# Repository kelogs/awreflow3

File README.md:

# AW reflow 3

awreflow3 is a reflow oven for soldering PCBs based on [Andy's Workshop awreflow2](http://andybrown.me.uk/2015/07/12/awreflow2/). Technically, this repository contains the missing electric diagram and a layout for the oven, with some modifications in order to suit the parts I had lying around. The purpose of this repository is that you can also pull the files and modify them according to your needs.

## Prerequisites

This project has been developed with [KiCad](http://www.kicad-pcb.org/download/)

## Notes

If you have to order the MOC3020 from the schematic you could get a [MOC3023](https://www.arrow.com/en/products/moc3023/isocom) instead and do away with the Q2 transistor and adjoining resistors.

Other things worth mentioning on the actual oven. Get one based on halogen heating elements just like Andy has done. Mine is a quartz elements oven and the PID is totally useless due to its very high inertia. I had to bypass the PID and hardcode some time intervals where power level is 0% and others where power is driven at 100%. 
At 1000W power and and 9L volume my oven can still bake a full tray of leaded solder PCBs, only a bit slower than others. Here is how it looks:

**NOTE** I currently have 9 extra PCBs already made. If you would like one drop me a message here and I'll deliver it for $3.44 + shipping + Paypal taxes

## License
[MIT](https://choosealicense.com/licenses/mit/)

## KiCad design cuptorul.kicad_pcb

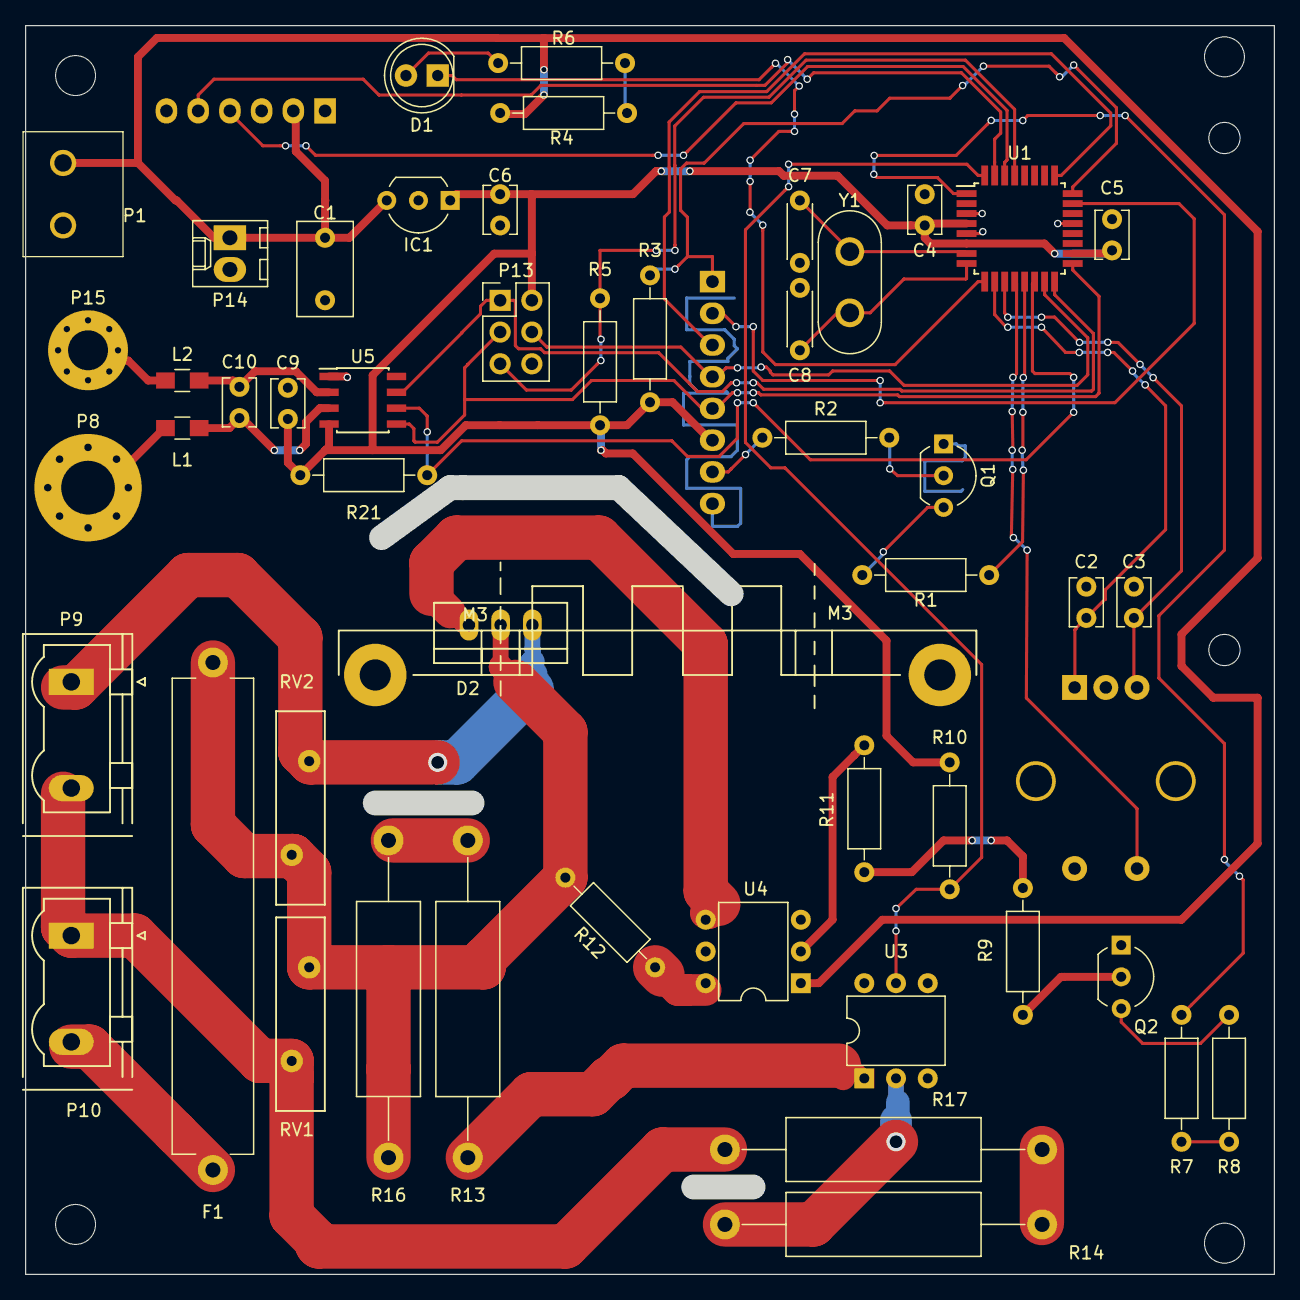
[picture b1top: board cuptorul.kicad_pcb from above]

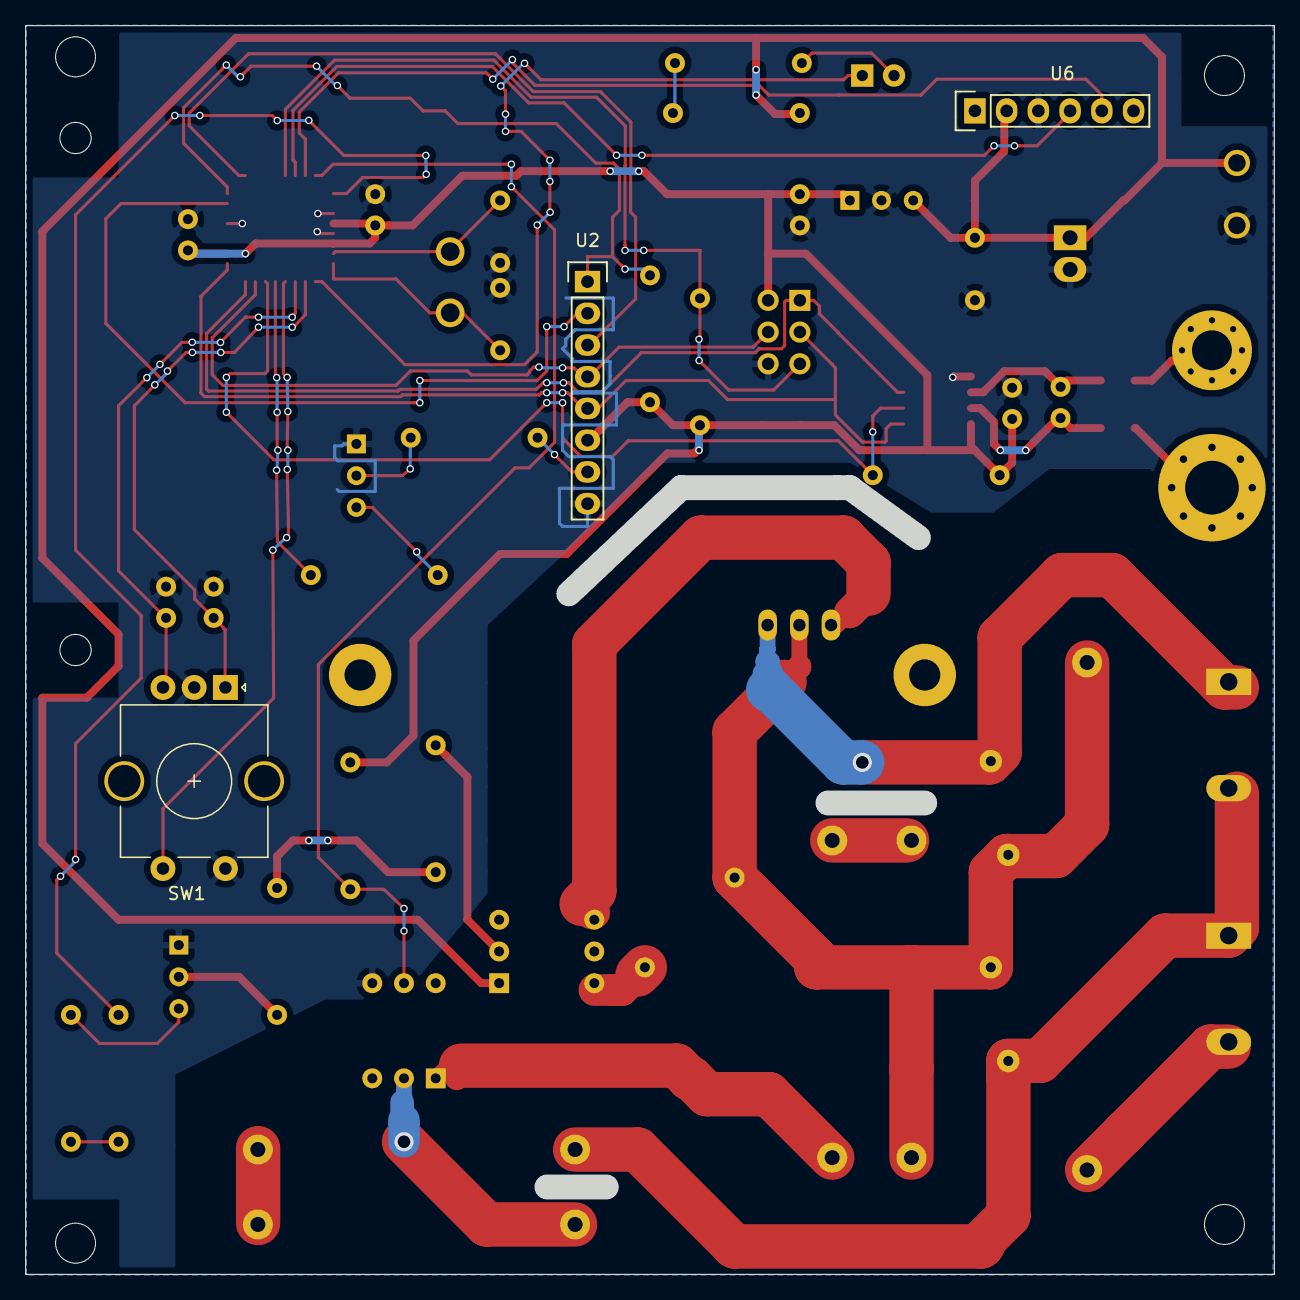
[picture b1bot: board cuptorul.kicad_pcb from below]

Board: 2 copper layers, 98.1 x 98.1 mm, 52 parts (3 on the bottom side), 46 nets.

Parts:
C1: 330nF; C_Disc_D7.5mm_W4.4mm_P5.00mm
C2, C3, C4, C5, C6, C9: 100nF; C_Disc_D3.8mm_W2.6mm_P2.50mm
C7, C8: 24pF; C_Disc_D4.3mm_W1.9mm_P5.00mm
C10: 10nF; C_Disc_D3.8mm_W2.6mm_P2.50mm
D1: LINK; LED_D5.0mm
D2: TRIAC; TO-220_Neutral123_Vertical
F1: Fuse; R_Axial_Power_L38.0mm_W6.4mm_P40.64mm
IC1: L78L33ACZ; TO-92_Inline_Wide
L1, L2: bead; L_0805_HandSoldering
P1: CONN_5V; em367502v
P8: CONN_TH_COUP_A; MountingHole_4.3mm_M4_Pad_Via
P9: CONN_OVEN; PhoenixContact_GMSTBVA-G_02x7.50mm_Vertical
P10: CONN_MAINS; PhoenixContact_GMSTBVA-G_02x7.50mm_Vertical
P13: CONN_ISP; Pin_Header_Straight_2x03_Pitch2.54mm
P14: CONN_FAN; Molex_KK-6410-02_02x2.54mm_Straight
P15: CONN_TH_COUP_B; MountingHole_3.2mm_M3_Pad_Via
Q1: C945; TO-92_Inline_Wide
Q2: C1815; TO-92_Inline_Wide
R1: 2k1 (1mA); R_Axial_DIN0207_L6.3mm_D2.5mm_P10.16mm_Horizontal
R2: 300 (10mA); R_Axial_DIN0207_L6.3mm_D2.5mm_P10.16mm_Horizontal
R3, R5, R10, R21: 10k; R_Axial_DIN0207_L6.3mm_D2.5mm_P10.16mm_Horizontal
R4, R6: 1k; R_Axial_DIN0207_L6.3mm_D2.5mm_P10.16mm_Horizontal
R7, R8: 300; R_Axial_DIN0207_L6.3mm_D2.5mm_P10.16mm_Horizontal
R9, R11: 47 (40mA); R_Axial_DIN0207_L6.3mm_D2.5mm_P10.16mm_Horizontal
R12: 360; R_Axial_DIN0207_L6.3mm_D2.5mm_P10.16mm_Horizontal
R13, R14, R16, R17: 10k; R_Axial_DIN0516_L15.5mm_D5.0mm_P25.40mm_Horizontal
RV1, RV2: Varistor; RV_Disc_D15.5_W3.9_P7.5
SW1: Rotary_Encoder_Switch; RotaryEncoder_Alps_EC11E-Switch_Vertical_H20mm_CircularMoun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
U1: ATMEGA88-20AU; TQFP-32_7x7mm_Pitch0.8mm
U2: NOKIA5110; Pin_Header_Straight_1x08
U3: OPTO-TRANSISTOR; DIP-6_W7.62mm
U4: MOC3020M; DIP-6_W7.62mm
U5: MAX31855KASA; SOIC-8_3.9x4.9mm_Pitch1.27mm
U6: HC-05-6pin-header; Pin_Header_Straight_1x06
Y1: Crystal; Crystal_HC50_Vertical

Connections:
+3V3: C4.1, C5.1, C6.2, C9.2, IC1.1, P13.2, R3.2, R5.1, R10.1, R21.1, U1.4, U1.6, U1.18, U2.6, U5.4
+5V: C1.2, IC1.3, P1.2, P14.1, R6.1, U4.1, U6.2
GND: C1.1, C2.1, C3.1, C4.2, C5.2, C6.1, C7.1, C8.1, C9.1, IC1.2, P1.1, P13.6, P14.2, Q1.1, Q2.1, SW1.2, SW1.4, U1.3, U1.5, U1.21, U2.8, U3.4, U5.1, U6.3
GNDPWR: P9.2, P10.1, R17.1, RV1.2
unnamed: C2.2, SW1.1, U1.10
unnamed: C3.2, SW1.3, U1.11
unnamed: C7.2, U1.7, Y1.1
unnamed: C8.2, U1.8, Y1.2
unnamed: C10.1, L2.2, U5.2
unnamed: C10.2, L1.2, U5.3
unnamed: D1.1, U1.9
unnamed: D1.2, R4.2
unnamed: D2.1, P9.1, RV2.2
unnamed: D2.2, F1.2, R12.2, R16.1, RV1.1, RV2.1
unnamed: D2.3, U4.4
unnamed: F1.1, P10.2
unnamed: L1.1, P8.1
unnamed: L2.1, P15.1
unnamed: SW1.5, U1.12
unnamed: U1.25, U2.3
unnamed: R3.1, U1.24, U2.1
unnamed: U1.23, U2.2
unnamed: R2.1, U2.7
unnamed: U1.31, U6.5
unnamed: U1.30, U6.4
unnamed: P13.1, U1.16, U5.7
unnamed: P13.3, U1.17, U2.5, U5.5
unnamed: P13.4, U1.15, U2.4
unnamed: P13.5, R5.2, U1.29
unnamed: Q1.2, R2.2
unnamed: Q1.3, R1.1
unnamed: Q2.2, R9.2
unnamed: Q2.3, R8.1
unnamed: R1.2, U1.13
unnamed: R4.1, R6.2
unnamed: R7.1, R8.2
unnamed: R7.2, U1.1
unnamed: R10.2, U1.32, U3.5
unnamed: R11.1, U4.2
unnamed: R9.1, R11.2
unnamed: R12.1, U4.6
unnamed: R13.1, R16.2
unnamed: R13.2, U3.1
unnamed: R14.1, R17.2
unnamed: R14.2, U3.2
unnamed: R21.2, U1.14, U5.6
